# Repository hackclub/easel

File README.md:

From now until the end of the school year (June 29), we're running a [programming language jam](https://langjam.hackclub.com), where you'll have the chance to win a signed copy of [Crafting Interpreters](https://craftinginterpreters.com/).

The gist: write a programming language &rarr; record a demo video and write a quick guide on how to get up and running with your programming language (including build instructions, if any!) &rarr; open a PR with a link to your repo containing these three things and your name, [#ship](https://hackclub.slack.com/archives/C0M8PUPU6) a demo on [Slack](https://hackclub.com/slack). Submission forms for the jam will open separately on June 29.

Check out [#building-programming-languages](https://app.slack.com/client/T0266FRGM/C06T22ZFQGP) on the Slack to hang out with fellow teenagers hacking on programming languages.

## Step zero: learn how to write a programming language!

**What if you don't know how to write a programming language?** Never fear, Orpheus the dinosaur to the rescue! We've written a guide on writing a programming language from scratch that'll teach you how to write a programming language called [Easel](https://easel.hackclub.com):

https://github.com/hackclub/easel/assets/59099858/9580bc79-933c-4c4d-b5f9-221af9adab2b

By the end of it, you'll have written a programming language and learned about how tree-walk interpreters work! Give it a spin at [https://easel.hackclub.com](https://easel.hackclub.com).

## Step one: write your programming language!

Here's the biggest part of the criteria:

- Minimally, should have the following features: variables, looping (think: for/while loops), conditional branching (think: if/else statements) and some form of recursion (think: functions). _Why? These are what make a programming language [Turing-complete](https://stackoverflow.com/questions/7284/what-is-turing-complete)_.

That's it! During the jam, the [community](https://hackclub.com/slack) will vote on what language does the following the best, including:

- Creativity and silliness! 
- Bonus points if you explain your implementation.

And the top three will get a hard copy of [Crafting Interpreters](https://craftinginterpreters.com/) while we're running our programming jam!

Read more about the criteria on [langjam.hackclub.com](https://langjam.hackclub.com).

## Step two: record a demo!

Record a demo of your programming language in action, for example using [Asciinema](https://asciinema.org/). Instructions can be found [here](https://docs.asciinema.org/getting-started/) for how to install Asciinema and then record your terminal with it. After you've got a recording of you running your programming language, grab the Asciinema link, which will look something like [https://asciinema.org/a/590145](https://asciinema.org/a/590145).

If you don't want to use Asciinema, that's perfectly fine! Check out [@Amin](https://hackclub.slack.com/team/U04PW2V355M)'s [programming lang](https://github.com/duckulus/minesketch) in Minecraft:

https://github.com/Duckulus/minesketch/assets/76813487/9075c54e-0dd9-4aa5-a6d1-a2f63ee824e3

Hopefully that gives you some crazy ideas.

## Step three: open a PR!

Open a PR by heading over to Pull requests and opening a PR. Your PR should have the following:

- [ ] A link to your repo, which should have an `examples` folder with at least one example other people can run and a README that describes how to build and run your repo and an explanation of the syntax and what makes it special.
- [ ] A copy of your repo inside a folder inside `languages`.
  
A good example to take a look at is [Arson](https://github.com/hackclub/easel/tree/main/languages/arson).

## Step four: get your stuff in the mail!

This one's easy. Wait for your stuff to come in the mail!

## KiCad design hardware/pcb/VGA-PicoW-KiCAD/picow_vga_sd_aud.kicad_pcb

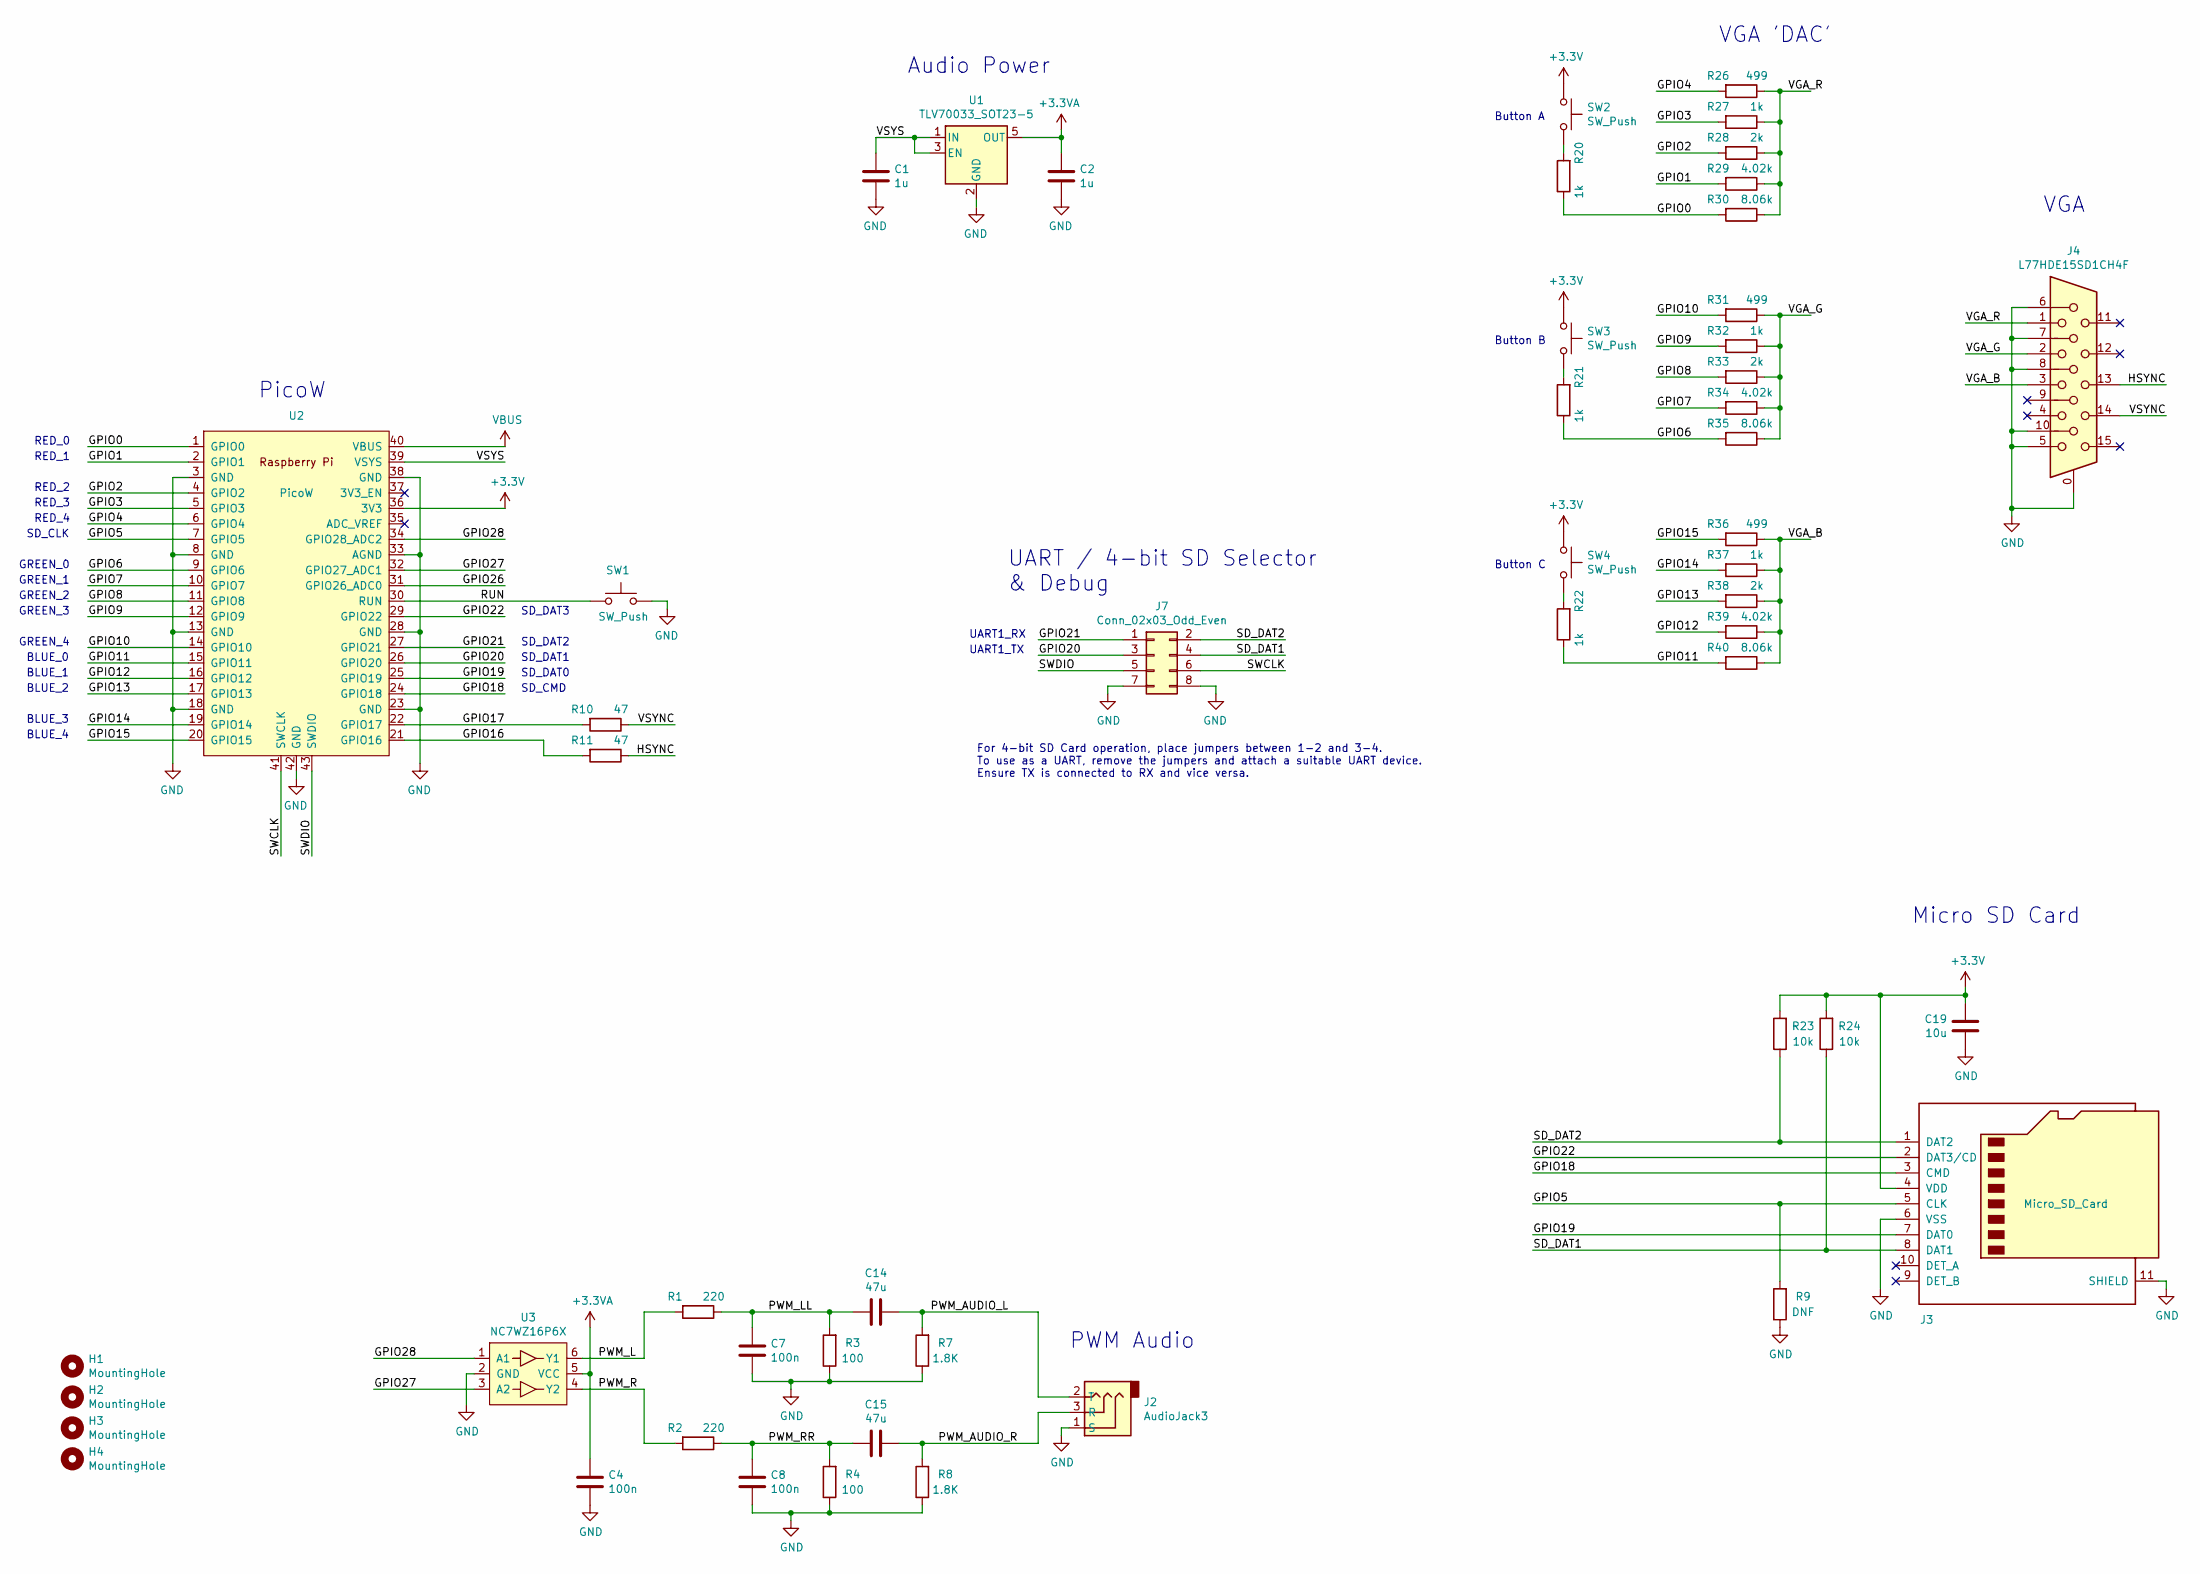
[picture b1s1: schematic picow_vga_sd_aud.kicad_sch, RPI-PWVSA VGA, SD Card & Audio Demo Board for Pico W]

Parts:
C1, C2: 1u; C_0603_1608Metric
C4, C7, C8: 100n; C_0402_1005Metric
C14, C15: 47u; C_0805_2012Metric
C19: 10u; C_0603_1608Metric
H1, H2, H3, H4: MountingHole; MountingHole_2.7mm_M2.5
J2: AudioJack3; CUI_SJ-3523-audio-jack
J3: Micro_SD_Card; microSD_HC_Molex_104031-0811
J4: L77HDE15SD1CH4F; DSUB-15-L77HDE15SD1CH4F
J7: Conn_02x03_Odd_Even; PinHeader_2x04_P2.54mm_Vertical
R1, R2: 220; R_0402_1005Metric
R3, R4: 100; R_0402_1005Metric
R7, R8: 1.8K; R_0402_1005Metric
R9: DNF; R_0402_1005Metric
R10, R11: 47; R_0402_1005Metric
R20, R21, R22, R27, R32, R37: 1k; R_0402_1005Metric
R23, R24: 10k; R_0402_1005Metric
R26, R31, R36: 499; R_0402_1005Metric
R28, R33, R38: 2k; R_0402_1005Metric
R29, R34, R39: 4.02k; R_0402_1005Metric
R30, R35, R40: 8.06k; R_0402_1005Metric
SW1, SW2, SW3, SW4: SW_Push; SW_Push_1P1T_NO_Vertical_Wuerth_434133025816
U1: TLV70033_SOT23-5; SOT-23-5
U2: PicoW; RPi_PicoW_SMD_TH
U3: NC7WZ16P6X; SOT-363_SC-70-6

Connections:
+3.3VA: C2.1, C4.1, U1.5 (OUT), U3.5 (VCC)
+3V3: C19.1, J3.4 (VDD), R23.2, R24.2, SW2.1, SW3.1, SW4.1, U2.36 (3V3)
/GPIO0: R20.1, R30.2, U2.1 (GPIO0)
/GPIO1: R29.2, U2.2 (GPIO1)
/GPIO2: R28.2, U2.4 (GPIO2)
/GPIO3: R27.2, U2.5 (GPIO3)
/GPIO4: R26.2, U2.6 (GPIO4)
/GPIO5: J3.5 (CLK), R9.2, U2.7 (GPIO5)
/GPIO6: R21.1, R35.2, U2.9 (GPIO6)
/GPIO7: R34.2, U2.10 (GPIO7)
/GPIO8: R33.2, U2.11 (GPIO8)
/GPIO9: R32.2, U2.12 (GPIO9)
/GPIO10: R31.2, U2.14 (GPIO10)
/GPIO11: R22.1, R40.2, U2.15 (GPIO11)
/GPIO12: R39.2, U2.16 (GPIO12)
/GPIO13: R38.2, U2.17 (GPIO13)
/GPIO14: R37.2, U2.19 (GPIO14)
/GPIO15: R36.2, U2.20 (GPIO15)
/GPIO16: R11.2, U2.21 (GPIO16)
/GPIO17: R10.2, U2.22 (GPIO17)
/GPIO18: J3.3 (CMD), U2.24 (GPIO18)
/GPIO19: J3.7 (DAT0), U2.25 (GPIO19)
/GPIO20: J7.3, U2.26 (GPIO20)
/GPIO21: J7.1, U2.27 (GPIO21)
/GPIO22: J3.2 (DAT3/CD), U2.29 (GPIO22)
/GPIO26: U2.31 (GPIO26_ADC0)
/GPIO27: U2.32 (GPIO27_ADC1), U3.3 (A2)
/GPIO28: U2.34 (GPIO28_ADC2), U3.1 (A1)
/HSYNC: J4.13, R11.1
/PWM_AUDIO_L: C14.1, J2.2 (T), R7.2
/PWM_AUDIO_R: C15.1, J2.3 (R), R8.2
/PWM_L: R1.2, U3.6 (Y1)
/PWM_LL: C7.1, C14.2, R1.1, R3.2
/PWM_R: R2.2, U3.4 (Y2)
/PWM_RR: C8.1, C15.2, R2.1, R4.2
/RUN: SW1.1, U2.30 (RUN)
/SD_DAT1: J3.8 (DAT1), J7.4, R24.1
/SD_DAT2: J3.1 (DAT2), J7.2, R23.1
/SWCLK: J7.6, U2.41 (SWCLK)
/SWDIO: J7.5, U2.43 (SWDIO)
/VGA_B: J4.3, R36.1, R37.1, R38.1, R39.1, R40.1
/VGA_G: J4.2, R31.1, R32.1, R33.1, R34.1, R35.1
/VGA_R: J4.1, R26.1, R27.1, R28.1, R29.1, R30.1
/VSYNC: J4.14, R10.1
/VSYS: C1.1, U1.1 (IN), U1.3 (EN), U2.39 (VSYS)
GND: C1.2, C2.2, C4.2, C7.2, C8.2, C19.2, J2.1 (S), J3.6 (VSS), J3.11 (SHIELD), J4.0, J4.5, J4.6, J4.7, J4.8, J4.10, J7.7, J7.8, R3.1, R4.1, R7.1, R8.1, R9.1, SW1.2, U1.2 (GND), U2.3 (GND), U2.8 (GND), U2.13 (GND), U2.18 (GND), U2.23 (GND), U2.28 (GND), U2.33 (AGND), U2.38 (GND), U2.42 (GND), U3.2 (GND)
unnamed: R20.2, SW2.2
unnamed: R21.2, SW3.2
unnamed: R22.2, SW4.2
VBUS: U2.40 (VBUS)

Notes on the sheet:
GREEN_0
RED_3
RED_1
SD_DAT2
Button A
VGA
SD_CLK
BLUE_4
BLUE_0
UART1_TX
SD_DAT1
RED_4
PicoW
For 4-bit SD Card operation, place jumpers between 1-2 and 3-4. To use as a UART, remove the jumpers and attach a suitable UART device. Ensure TX is connected to RX and vice versa.
UART1_RX
VGA 'DAC'
Button B
Button C
GREEN_1
UART / 4-bit SD Selector & Debug
SD_DAT0
BLUE_3
SD_CMD
SD_DAT3
Micro SD Card
GREEN_4
RED_2
GREEN_2
Audio Power
PWM Audio
BLUE_1
GREEN_3
BLUE_2
RED_0

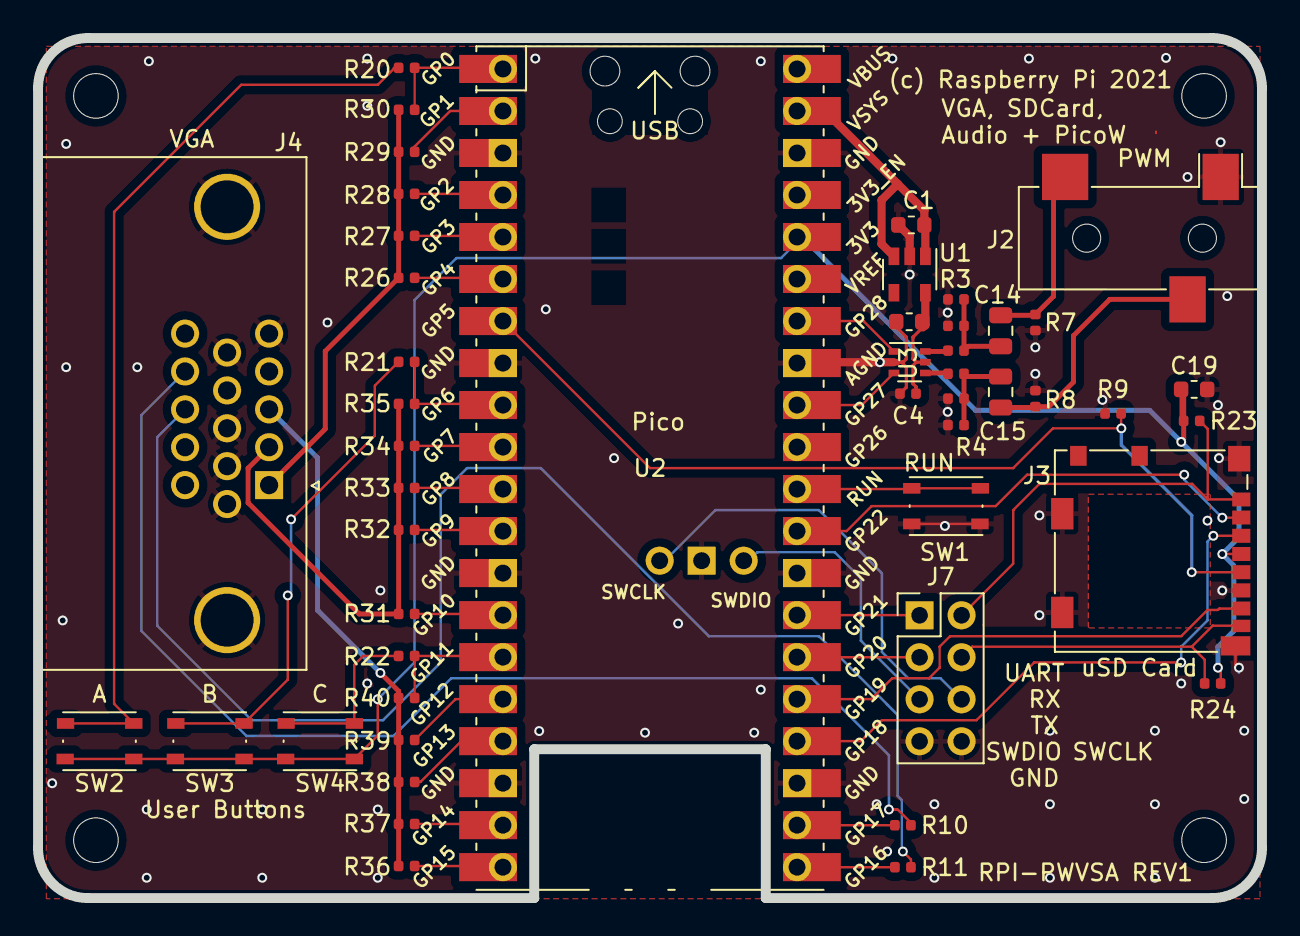
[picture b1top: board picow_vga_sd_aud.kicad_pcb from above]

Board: 4 copper layers, 74.0 x 52.0 mm, 52 parts (0 on the bottom side), 48 nets.

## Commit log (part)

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2024-04-16 Work on interactive
2024-04-16 Parser done
2024-04-16 Current progress on first two parts
2024-04-17 Begin interpreter
2024-04-17 Progress
2024-04-18 Easel done
2024-04-18 Cleanup
2024-04-18 Make more progress
2024-04-18 Route
2024-04-19 Interpreter draft done
2024-04-19 Finish parser draft
2024-04-19 First draft done
2024-04-19 Tweak
2024-04-19 Parentheses
2024-04-29 Fixed table of contents
2024-04-30 Code works
2024-05-01 Get canvas working
2024-05-01 Canvas done
2024-05-01 Media queries
2024-05-02 Set up Nodebox
2024-05-03 Kill shell after running
2024-05-06 Start writing
2024-05-06 Need a break from queries
2024-05-07 First part mostly done
2024-05-08 Begin branding
2024-05-08 Move to languages
2024-05-08 Branding
2024-05-08 Up to date
2024-05-08 Done with initial part
2024-05-09 HTML sandbox works
2024-05-09 Add analytics
2024-05-09 Easel shows up in editor
2024-05-09 Submission form done
2024-05-10 v1 to ship
2024-05-10 Update embed image
2024-05-10 Update meta
2024-05-10 Done
2024-05-13 Update alert
2024-05-14 Fix typos
2024-05-16 Minor grammar edit
2024-05-16 Minor grammar edits
2024-05-16 Add sticker form
2024-05-16 Move address line
2024-05-16 Tighten stickers CTA
2024-05-16 Update languages
2024-05-16 Compress embed
2024-05-16 Move embed to CDN
2024-05-16 Update embed
2024-05-20 Fix PR placeholder and missing guide links
2024-05-21 Add elation language
2024-05-21 Add hours field
2024-05-22 Fix instructions table
2024-05-23 [BUG] - Update orpheus-writes-lexer.mdx to fix broken link at line 3376.
    Changed the permalink to lexer.js to [here](https://github.com/hackclub/easel/blob/main/languages/easel/lexer.js) !
2024-06-01 Update banner
2024-06-01 langjam
2024-06-03 Add more instructions
2024-06-05 Required fields
2024-07-03 Added h4x to languages folder
2024-07-03 Add Eia64 Language
2024-07-03 monopolang
2024-07-18 added in meowLang
2024-07-27 Added nil repo in languages folder
    https://github.com/achester88/nil
2024-07-28 Add treestack to languages folder
2024-08-01 Added function hell lang
2024-08-01 Add Fateful
2024-08-02 Add Eia64
2024-08-02 Remove folder
2024-08-03 Update repo
2024-08-04 Add Inumaki
2026-05-14 Bump immutable from 4.3.5 to 4.3.8 in /site
    Bumps [immutable](https://github.com/immutable-js/immutable-js) from 4.3.5 to 4.3.8.
    - [Release notes](https://github.com/immutable-js/immutable-js/releases)
    - [Changelog](https://github.com/immutable-js/immutable-js/blob/main/CHANGELOG.md)
    - [Commits](https://github.com/immutable-js/immutable-js/compare/v4.3.5...v4.3.8)
    ---
    updated-dependencies:
2026-05-14 Bump minimatch from 3.1.2 to 3.1.5 in /site
    Bumps [minimatch](https://github.com/isaacs/minimatch) from 3.1.2 to 3.1.5.
    - [Changelog](https://github.com/isaacs/minimatch/blob/main/changelog.md)
    - [Commits](https://github.com/isaacs/minimatch/compare/v3.1.2...v3.1.5)
    ---
    updated-dependencies:
    - dependency-name: minimatch
2026-05-14 Bump rollup from 4.17.2 to 4.59.0 in /site
    Bumps [rollup](https://github.com/rollup/rollup) from 4.17.2 to 4.59.0.
    - [Release notes](https://github.com/rollup/rollup/releases)
    - [Changelog](https://github.com/rollup/rollup/blob/master/CHANGELOG.md)
    - [Commits](https://github.com/rollup/rollup/compare/v4.17.2...v4.59.0)
    ---
    updated-dependencies:
2026-05-14 Bump mermaid from 10.9.0 to 10.9.6 in /site
    Bumps [mermaid](https://github.com/mermaid-js/mermaid) from 10.9.0 to 10.9.6.
    - [Release notes](https://github.com/mermaid-js/mermaid/releases)
    - [Commits](https://github.com/mermaid-js/mermaid/compare/v10.9.0...v10.9.6)
    ---
    updated-dependencies:
    - dependency-name: mermaid
2026-05-15 feat: remove outdated banner on top of page
2026-05-15 Bump rand from 0.8.5 to 0.8.6 in /languages/treestack
    Bumps [rand](https://github.com/rust-random/rand) from 0.8.5 to 0.8.6.
    - [Release notes](https://github.com/rust-random/rand/releases)
    - [Changelog](https://github.com/rust-random/rand/blob/0.8.6/CHANGELOG.md)
    - [Commits](https://github.com/rust-random/rand/compare/0.8.5...0.8.6)
    ---
    updated-dependencies:
2026-05-15 Bump next-mdx-remote from 4.4.1 to 6.0.0 in /site
    Bumps [next-mdx-remote](https://github.com/hashicorp/next-mdx-remote) from 4.4.1 to 6.0.0.
    - [Release notes](https://github.com/hashicorp/next-mdx-remote/releases)
    - [Changelog](https://github.com/hashicorp/next-mdx-remote/blob/main/CHANGELOG.md)
    - [Commits](https://github.com/hashicorp/next-mdx-remote/compare/v4.4.1...v6.0.0)
    ---
    updated-dependencies:
2026-05-18 fix: deployment issues
2026-05-20 chore: bump next-mdx-remote to 6.0.0
2026-05-20 Bump next from 14.2.1 to 15.5.18 in /site
    Bumps [next](https://github.com/vercel/next.js) from 14.2.1 to 15.5.18.
    - [Release notes](https://github.com/vercel/next.js/releases)
    - [Changelog](https://github.com/vercel/next.js/blob/canary/release.js)
    - [Commits](https://github.com/vercel/next.js/compare/v14.2.1...v15.5.18)
    ---
    updated-dependencies:
2026-05-26 Bump electron from 31.1.0 to 39.8.5 in /languages/functionhell/editor
    Bumps [electron](https://github.com/electron/electron) from 31.1.0 to 39.8.5.
    - [Release notes](https://github.com/electron/electron/releases)
    - [Commits](https://github.com/electron/electron/compare/v31.1.0...v39.8.5)
    ---
    updated-dependencies:
    - dependency-name: electron
2026-06-17 Bump dompurify from 3.4.3 to 3.4.10 in /site
    Bumps [dompurify](https://github.com/cure53/DOMPurify) from 3.4.3 to 3.4.10.
    - [Release notes](https://github.com/cure53/DOMPurify/releases)
    - [Commits](https://github.com/cure53/DOMPurify/compare/3.4.3...3.4.10)
    ---
    updated-dependencies:
    - dependency-name: dompurify
2026-06-18 Bump dompurify from 3.4.3 to 3.4.11 in /site
    Bumps [dompurify](https://github.com/cure53/DOMPurify) from 3.4.3 to 3.4.11.
    - [Release notes](https://github.com/cure53/DOMPurify/releases)
    - [Commits](https://github.com/cure53/DOMPurify/compare/3.4.3...3.4.11)
    ---
    updated-dependencies:
    - dependency-name: dompurify
2026-06-23 Bump ws from 8.20.1 to 8.21.0 in /site
    Bumps [ws](https://github.com/websockets/ws) from 8.20.1 to 8.21.0.
    - [Release notes](https://github.com/websockets/ws/releases)
    - [Commits](https://github.com/websockets/ws/compare/8.20.1...8.21.0)
    ---
    updated-dependencies:
    - dependency-name: ws
2026-06-28 Bump js-yaml from 4.1.1 to 4.3.0 in /site
    Bumps [js-yaml](https://github.com/nodeca/js-yaml) from 4.1.1 to 4.3.0.
    - [Changelog](https://github.com/nodeca/js-yaml/blob/4.3.0/CHANGELOG.md)
    - [Commits](https://github.com/nodeca/js-yaml/compare/4.1.1...4.3.0)
    ---
    updated-dependencies:
    - dependency-name: js-yaml

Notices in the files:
hardware/pcb/VGA-PicoW-KiCAD/picow_vga_sd_aud.kicad_sch:
(c) 2022 Raspberry Pi Ltd
